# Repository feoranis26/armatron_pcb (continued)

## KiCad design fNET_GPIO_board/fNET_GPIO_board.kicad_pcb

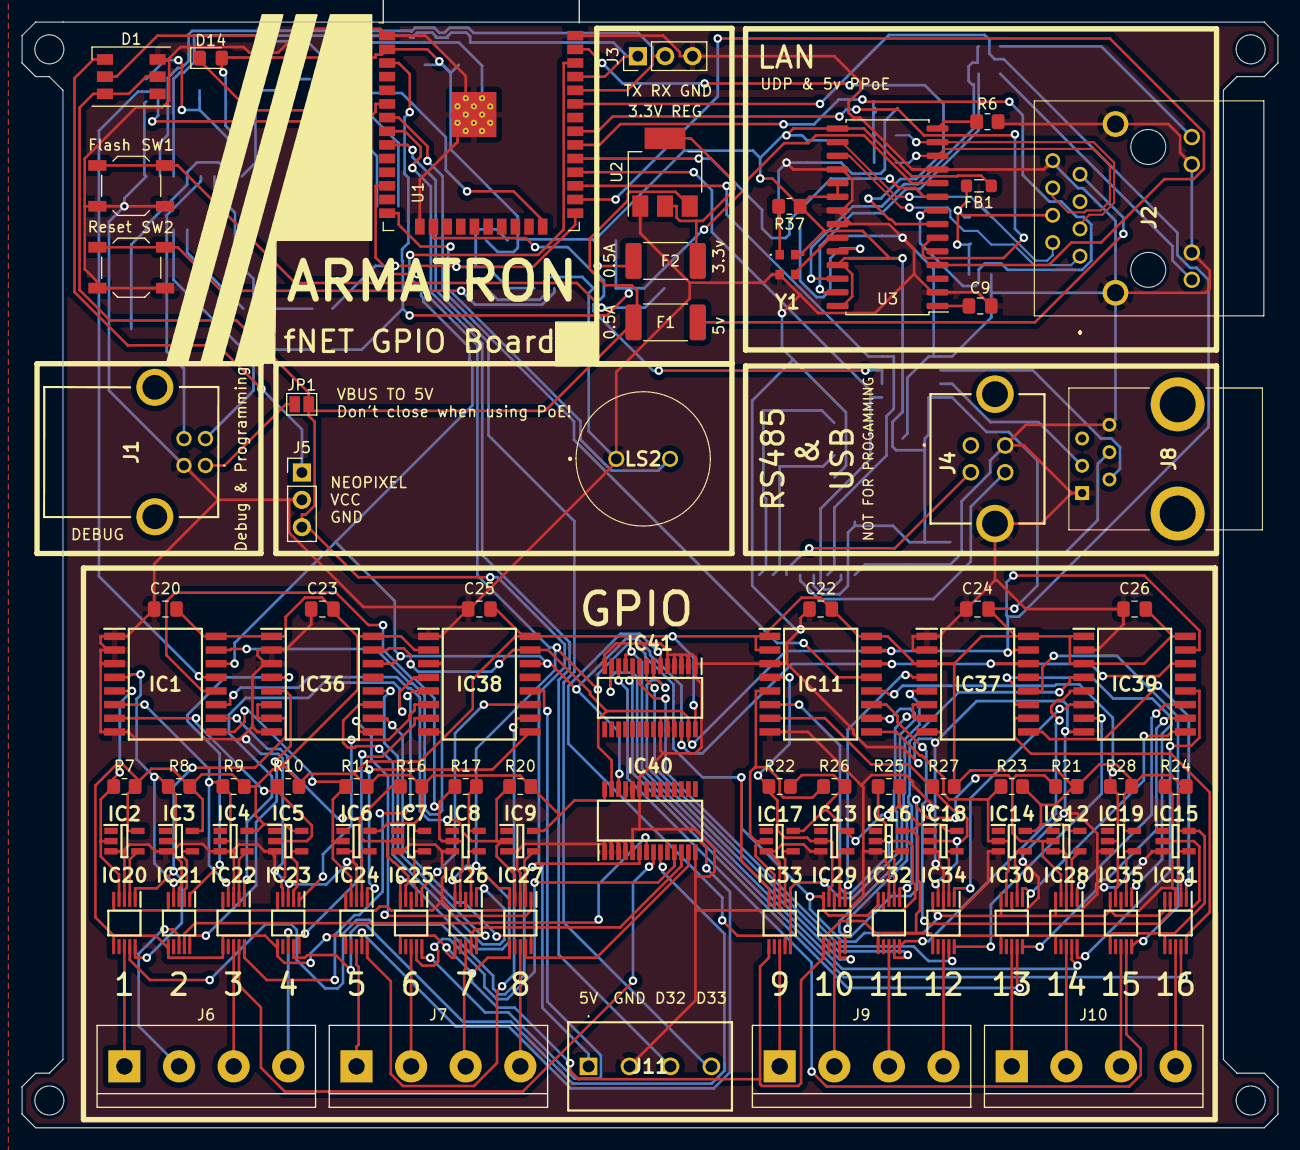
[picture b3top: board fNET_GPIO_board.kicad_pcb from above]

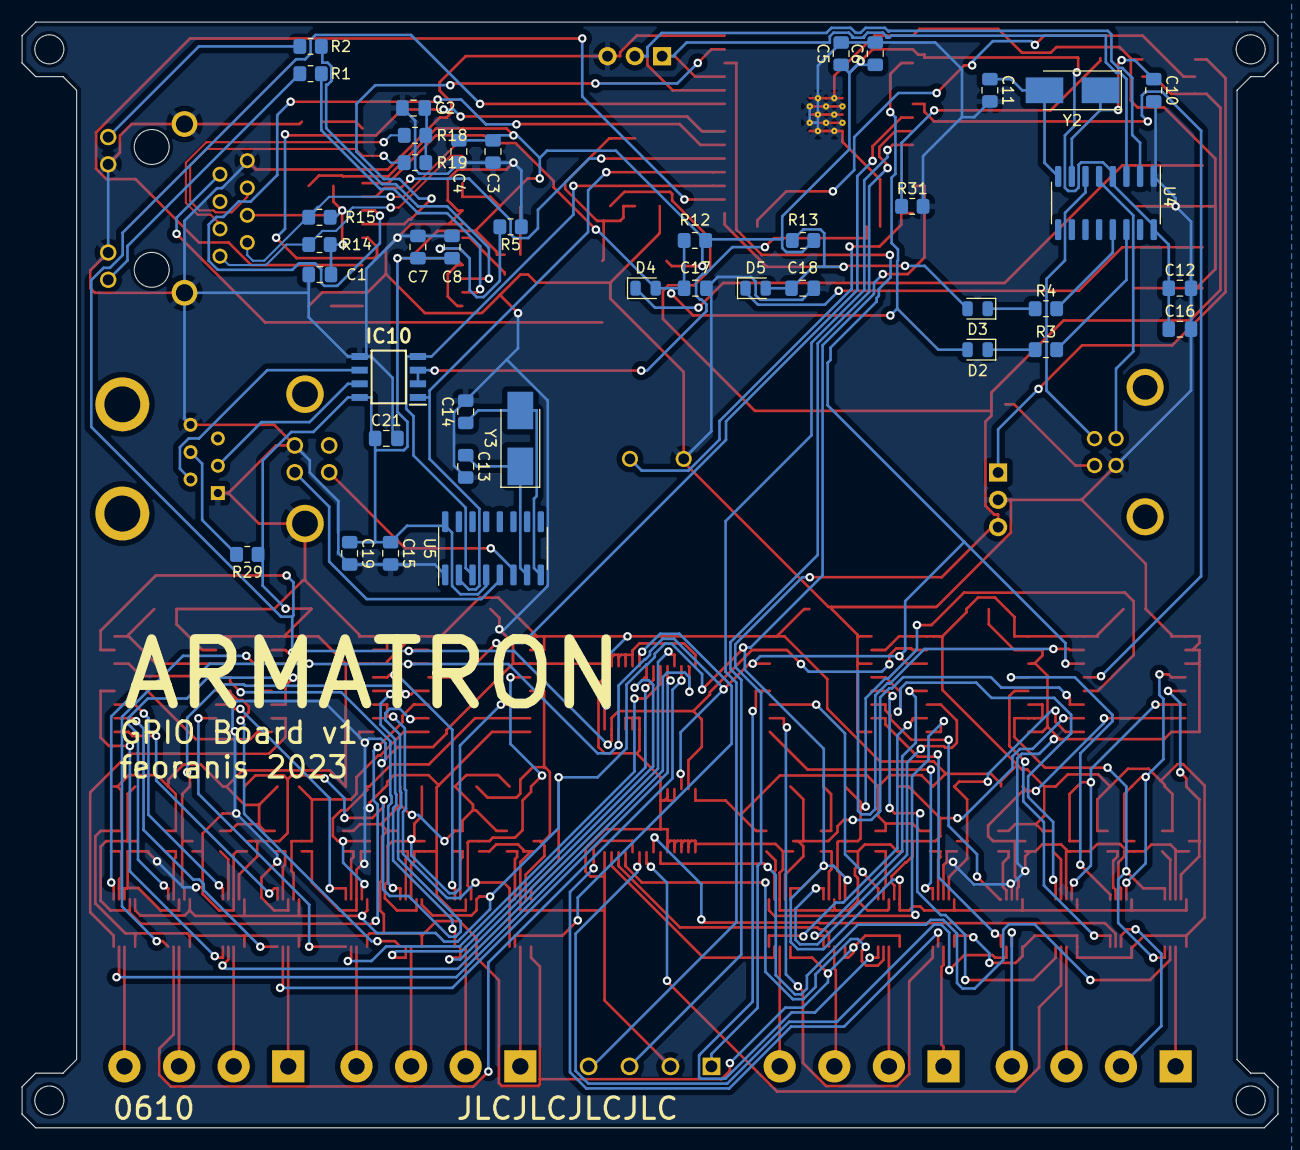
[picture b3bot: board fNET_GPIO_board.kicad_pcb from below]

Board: 2 copper layers, 116.8 x 102.9 mm, 134 parts (41 on the bottom side), 155 nets.

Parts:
C1, C2: 0.1uF; C_0805_2012Metric_Pad1.18x1.45mm_HandSolder
C3, C6, C7, C16, C17, C18, C19: 100n; C_0805_2012Metric_Pad1.18x1.45mm_HandSolder
C4, C8, C9: 10uF; C_0805_2012Metric_Pad1.18x1.45mm_HandSolder
C5: 10u; C_0805_2012Metric_Pad1.18x1.45mm_HandSolder
C10, C11, C13, C14: 22pF; C_0805_2012Metric_Pad1.18x1.45mm_HandSolder
C12, C15: 4.7u; C_0805_2012Metric_Pad1.18x1.45mm_HandSolder
C20, C21, C22, C23, C24, C25, C26: 1uf; C_0805_2012Metric_Pad1.18x1.45mm_HandSolder
D1: Inolux_IN-PI556FCH; LED_WS2812_PLCC6_5.0x5.0mm_P1.6mm
D2, D3, D4, D5: D; D_0805_2012Metric
D14: LED_Small; LED_0805_2012Metric_Pad1.15x1.40mm_HandSolder
F1, F2: 0.5A; Fuse_2512_6332Metric_Pad1.52x3.35mm_HandSolder
FB1: FerriteBead_Small; L_0805_2012Metric_Pad1.05x1.20mm_HandSolder
H1, H2, H3, H4: MountingHole; MountingHole_2.7mm_M2.5
IC1, IC11, IC36, IC37, IC38, IC39: PCF8574T_3,518; SOIC127P1032X265-16N
IC2, IC3, IC4, IC5, IC6, IC7, IC8, IC9, IC12, IC13, IC14, IC15, IC16, IC17, IC18, IC19: M74VHC1GT50DTT1G; SOT95P275X110-5N
IC10: MAX485ESA+; SOIC127P600X175-8N
IC20, IC21, IC22, IC23, IC24, IC25, IC26, IC27, IC28, IC29, IC30, IC31, IC32, IC33, IC34, IC35: MAX4634EUB+; SOP50P490X110-10N
IC40, IC41: PCA9685PW,118; SOP65P640X110-28N
J1: USB_B; USB1030GFPBB
J2: 5-2337992-4; 523379924
J3, J5: Conn_01x03_Pin; PinHeader_1x03_P2.54mm_Vertical
J4: USB_B; M701-330442
J6, J7, J9, J10: Screw_Terminal_01x04; TerminalBlock_bornier-4_P5.08mm
J8: 87180-064LF; 87180064LF
J11: Screw_Terminal_01x04; 2843924
JP1: SolderJumper_2_Open; SolderJumper-2_P1.3mm_Open_Pad1.0x1.5mm
LS2: PT-1241PFQ; PT1241PFQ
R1, R2: 220R; R_0805_2012Metric_Pad1.20x1.40mm_HandSolder
R3, R4, R5, R12, R13, R29, R37: 10K; R_0805_2012Metric_Pad1.20x1.40mm_HandSolder
R6: 2.32K 1%; R_0805_2012Metric_Pad1.20x1.40mm_HandSolder
R7, R8, R9, R10, R11, R16, R17, R20, R21, R22, R23, R24, R25, R26, R27, R28, R31: 1K; R_0805_2012Metric_Pad1.20x1.40mm_HandSolder
R14, R15, R18, R19: 50R; R_0805_2012Metric_Pad1.20x1.40mm_HandSolder
SW1, SW2: SW_Push; SW_SPST_TL3342
U1: ESP32-WROOM-32
U2: AMS1117-3.3; SOT-223-3_TabPin2
U3: ENC28J60x-SO; SOIC-28W_7.5x17.9mm_P1.27mm
U4, U5: CH340G; SOIC-16_3.9x9.9mm_P1.27mm
Y1: ECS-2520MVLC-250-BN-TR3; ECS2520MVLC250BNTR3
Y2, Y3: 12MHz; Crystal_SMD_5032-2Pin_5.0x3.2mm_HandSoldering

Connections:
+3.3V: C3.1, C4.1, C5.1, C6.1, C7.1, C8.1, C12.1, C15.1, C16.1, C19.1, C20.1, C21.1, C22.1, C23.1, C24.1, C25.1, C26.1, D14.2 (A), F2.2, FB1.1, IC1.16 (VDD), IC2.5 (VCC), IC3.5 (VCC), IC4.5 (VCC), IC5.5 (VCC), IC6.5 (VCC), IC7.5 (VCC), IC8.5 (VCC), IC9.5 (VCC), IC10.8 (VCC), IC11.1 (A0), IC11.2 (A1), IC11.16 (VDD), IC12.5 (VCC), IC13.5 (VCC), IC14.5 (VCC), IC15.5 (VCC), IC16.5 (VCC), IC17.5 (VCC), IC18.5 (VCC), IC19.5 (VCC), IC20.6 (V+), IC21.6 (V+), IC22.6 (V+), IC23.6 (V+), IC24.6 (V+), IC25.6 (V+), IC26.6 (V+), IC27.6 (V+), IC28.6 (V+), IC29.6 (V+), IC30.6 (V+), IC31.6 (V+), IC32.6 (V+), IC33.6 (V+), IC34.6 (V+), IC35.6 (V+), IC36.1 (A0), IC36.16 (VDD), IC37.3 (A2), IC37.16 (VDD), IC38.2 (A1), IC38.16 (VDD), IC39.1 (A0), IC39.3 (A2), IC39.16 (VDD), IC40.28 (VDD), IC41.28 (VDD), R7.1, R8.1, R9.1, R10.1, R11.1, R12.1, R13.1, R16.1, R17.1, R20.1, R21.1, R22.1, R23.1, R24.1, R25.1, R26.1, R27.1, R28.1, R29.1, R37.1, U1.2 (VDD), U3.15 (VDDTX), U3.19 (VDDRX), U3.20 (VDDPLL), U3.25 (VDDOSC), U3.28 (VDD), U4.4 (V3), U4.16 (VCC), U5.4 (V3), U5.16 (VCC), Y1.4 (VDD)
+5V: D1.3 (VDD), D1.5 (VCC), F1.1, J5.3, J11.1, JP1.2 (B), U2.3 (VI)
/Ethernet/LEDA: R1.2, U3.27 (LEDA)
/Ethernet/LEDB: R2.2, U3.26 (LEDB)
/Ethernet/RX+: J2.P3, R18.1, U3.13 (TPIN+)
/Ethernet/RX-: J2.P6, R19.2, U3.12 (TPIN-)
/Ethernet/TPOUT+: J2.P1, R14.2, U3.17 (TPOUT+)
/Ethernet/TPOUT-: J2.P2, R15.1, U3.16 (TPOUT-)
/Ethernet/TX_CT: C1.1, FB1.2, J2.P4, R14.1, R15.2
/GPIO Extender 1/GPIO Mux 0/A0: IC21.1 (A0), IC36.4 (P0)
/GPIO Extender 1/GPIO Mux 0/A1: IC21.10 (A1), IC36.5 (P1)
/GPIO Extender 1/GPIO Mux 0/IN: IC1.4 (P0), IC3.2 (INA), IC21.4 (NO3), R8.2
/GPIO Extender 1/GPIO Mux 1/A0: IC20.1 (A0), IC20.10 (A1), IC36.6 (P2), IC36.7 (P3)
/GPIO Extender 1/GPIO Mux 1/IN: IC1.5 (P1), IC2.2 (INA), IC20.4 (NO3), R7.2
/GPIO Extender 1/GPIO Mux 2/A0: IC22.1 (A0), IC38.4 (P0)
/GPIO Extender 1/GPIO Mux 2/A1: IC22.10 (A1), IC38.5 (P1)
/GPIO Extender 1/GPIO Mux 2/IN: IC1.6 (P2), IC4.2 (INA), IC22.4 (NO3), R9.2
/GPIO Extender 1/GPIO Mux 3/A0: IC23.1 (A0), IC38.6 (P2)
/GPIO Extender 1/GPIO Mux 3/A1: IC23.10 (A1), IC38.7 (P3)
/GPIO Extender 1/GPIO Mux 3/IN: IC1.7 (P3), IC5.2 (INA), IC23.4 (NO3), R10.2
/GPIO Extender 1/GPIO Mux 4/A0: IC24.1 (A0), IC38.9 (P4)
/GPIO Extender 1/GPIO Mux 4/A1: IC24.10 (A1), IC38.10 (P5)
/GPIO Extender 1/GPIO Mux 4/IN: IC1.9 (P4), IC6.2 (INA), IC24.4 (NO3), R11.2
/GPIO Extender 1/GPIO Mux 5/A0: IC25.1 (A0), IC38.11 (P6)
/GPIO Extender 1/GPIO Mux 5/A1: IC25.10 (A1), IC38.12 (P7)
/GPIO Extender 1/GPIO Mux 5/IN: IC1.10 (P5), IC7.2 (INA), IC25.4 (NO3), R16.2
/GPIO Extender 1/GPIO Mux 6/A0: IC27.1 (A0), IC36.9 (P4)
/GPIO Extender 1/GPIO Mux 6/A1: IC27.10 (A1), IC36.10 (P5)
/GPIO Extender 1/GPIO Mux 6/IN: IC1.11 (P6), IC9.2 (INA), IC27.4 (NO3), R20.2
/GPIO Extender 1/GPIO Mux 7/A0: IC26.1 (A0), IC36.11 (P6)
/GPIO Extender 1/GPIO Mux 7/A1: IC26.10 (A1), IC36.12 (P7)
/GPIO Extender 1/GPIO Mux 7/IN: IC1.12 (P7), IC8.2 (INA), IC26.4 (NO3), R17.2
/GPIO Extender 1/OUT_1: IC20.8 (COM), J6.1
/GPIO Extender 1/OUT_2: IC21.8 (COM), J6.2
/GPIO Extender 1/OUT_3: IC22.8 (COM), J6.3
/GPIO Extender 1/OUT_4: IC23.8 (COM), J6.4
/GPIO Extender 1/OUT_5: IC24.8 (COM), J7.1
/GPIO Extender 1/OUT_6: IC25.8 (COM), J7.2
/GPIO Extender 1/OUT_7: IC26.8 (COM), J7.3
/GPIO Extender 1/OUT_8: IC27.8 (COM), J7.4
/GPIO Extender 1/PWM_0: IC20.9 (NO2), IC40.6 (LED0)
/GPIO Extender 1/PWM_1: IC21.9 (NO2), IC40.7 (LED1)
/GPIO Extender 1/PWM_2: IC22.9 (NO2), IC40.8 (LED2)
/GPIO Extender 1/PWM_3: IC23.9 (NO2), IC40.9 (LED3)
/GPIO Extender 1/PWM_4: IC24.9 (NO2), IC40.10 (LED4)
/GPIO Extender 1/PWM_5: IC25.9 (NO2), IC40.11 (LED5)
/GPIO Extender 1/PWM_6: IC26.9 (NO2), IC40.12 (LED6)
/GPIO Extender 1/PWM_7: IC27.9 (NO2), IC40.13 (LED7)
/GPIO Extender 2/GPIO Mux 0/A0: IC29.1 (A0), IC37.4 (P0)
/GPIO Extender 2/GPIO Mux 0/A1: IC29.10 (A1), IC37.5 (P1)
/GPIO Extender 2/GPIO Mux 0/IN: IC11.4 (P0), IC13.2 (INA), IC29.4 (NO3), R22.2
/GPIO Extender 2/GPIO Mux 1/A0: IC33.1 (A0), IC33.10 (A1), IC37.6 (P2), IC37.7 (P3)
/GPIO Extender 2/GPIO Mux 1/IN: IC11.5 (P1), IC17.2 (INA), IC33.4 (NO3), R26.2
/GPIO Extender 2/GPIO Mux 2/A0: IC32.1 (A0), IC39.4 (P0)
/GPIO Extender 2/GPIO Mux 2/A1: IC32.10 (A1), IC39.5 (P1)
/GPIO Extender 2/GPIO Mux 2/IN: IC11.6 (P2), IC16.2 (INA), IC32.4 (NO3), R25.2
/GPIO Extender 2/GPIO Mux 3/A0: IC34.1 (A0), IC39.6 (P2)
/GPIO Extender 2/GPIO Mux 3/A1: IC34.10 (A1), IC39.7 (P3)
/GPIO Extender 2/GPIO Mux 3/IN: IC11.7 (P3), IC18.2 (INA), IC34.4 (NO3), R27.2
/GPIO Extender 2/GPIO Mux 4/A0: IC30.1 (A0), IC39.9 (P4)
/GPIO Extender 2/GPIO Mux 4/A1: IC30.10 (A1), IC39.10 (P5)
/GPIO Extender 2/GPIO Mux 4/IN: IC11.9 (P4), IC14.2 (INA), IC30.4 (NO3), R23.2
/GPIO Extender 2/GPIO Mux 5/A0: IC28.1 (A0), IC39.11 (P6)
/GPIO Extender 2/GPIO Mux 5/A1: IC28.10 (A1), IC39.12 (P7)
/GPIO Extender 2/GPIO Mux 5/IN: IC11.10 (P5), IC12.2 (INA), IC28.4 (NO3), R21.2
/GPIO Extender 2/GPIO Mux 6/A0: IC31.1 (A0), IC37.9 (P4)
/GPIO Extender 2/GPIO Mux 6/A1: IC31.10 (A1), IC37.10 (P5)
/GPIO Extender 2/GPIO Mux 6/IN: IC11.11 (P6), IC15.2 (INA), IC31.4 (NO3), R24.2
/GPIO Extender 2/GPIO Mux 7/A0: IC35.1 (A0), IC37.11 (P6)
/GPIO Extender 2/GPIO Mux 7/A1: IC35.10 (A1), IC37.12 (P7)
/GPIO Extender 2/GPIO Mux 7/IN: IC11.12 (P7), IC19.2 (INA), IC35.4 (NO3), R28.2
/GPIO Extender 2/OUT_1: IC33.8 (COM), J9.1
/GPIO Extender 2/OUT_2: IC29.8 (COM), J9.2
/GPIO Extender 2/OUT_3: IC32.8 (COM), J9.3
/GPIO Extender 2/OUT_4: IC34.8 (COM), J9.4
/GPIO Extender 2/OUT_5: IC30.8 (COM), J10.1
/GPIO Extender 2/OUT_6: IC28.8 (COM), J10.2
/GPIO Extender 2/OUT_7: IC35.8 (COM), J10.3
/GPIO Extender 2/OUT_8: IC31.8 (COM), J10.4
/GPIO Extender 2/PWM_0: IC33.9 (NO2), IC41.6 (LED0)
/GPIO Extender 2/PWM_1: IC29.9 (NO2), IC41.7 (LED1)
/GPIO Extender 2/PWM_2: IC32.9 (NO2), IC41.8 (LED2)
/GPIO Extender 2/PWM_3: IC34.9 (NO2), IC41.9 (LED3)
/GPIO Extender 2/PWM_4: IC30.9 (NO2), IC41.10 (LED4)
/GPIO Extender 2/PWM_5: IC28.9 (NO2), IC41.11 (LED5)
/GPIO Extender 2/PWM_6: IC35.9 (NO2), IC41.12 (LED6)
/GPIO Extender 2/PWM_7: IC31.9 (NO2), IC41.13 (LED7)
/Serial/A: IC10.6 (A), J8.2
/Serial/B: IC10.7 (B), J8.3
/Serial/INTR: J8.4, R29.2
/USB/VBUS: J1.1 (VBUS), JP1.1 (A)
/USB/nDTR: R4.2, U4.13 (~DTR)
/USB/nRTS: R3.2, U4.14 (~RTS)
DE: IC10.2 (~RE), IC10.3 (DE), U1.16 (IO13)
ETH_CS: U1.29 (IO5), U3.9 (~CS)
ETH_INTER: U1.26 (IO4), U3.4 (~INT)
EX1_INT: IC1.13 (~INT), U1.6 (IO34)
EX2_INT: IC11.13 (~INT), U1.7 (IO35)
FLASH_UART: D3.1 (K), R4.1
GND: C1.2, C2.2, C3.2, C4.2, C5.2, C6.2, C7.2, C8.2, C9.2, C10.2, C11.2, C12.2, C13.2, C14.2, C15.2, C16.2, C17.2, C18.2, C19.2, C20.2, C21.2, C22.2, C23.2, C24.2, C25.2, C26.2, D1.6 (VSS), IC1.1 (A0), IC1.2 (A1), IC1.3 (A2), IC1.8 (VSS), IC2.3 (GND), IC3.3 (GND), IC4.3 (GND), IC5.3 (GND), IC6.3 (GND), IC7.3 (GND), IC8.3 (GND), IC9.3 (GND), IC10.5 (GND), IC11.3 (A2), IC11.8 (VSS), IC12.3 (GND), IC13.3 (GND), IC14.3 (GND), IC15.3 (GND), IC16.3 (GND), IC17.3 (GND), IC18.3 (GND), IC19.3 (GND), IC20.3 (GND), IC21.3 (GND), IC22.3 (GND), IC23.3 (GND), IC24.3 (GND), IC25.3 (GND), IC26.3 (GND), IC27.3 (GND), IC28.3 (GND), IC29.3 (GND), IC30.3 (GND), IC31.3 (GND), IC32.3 (GND), IC33.3 (GND), IC34.3 (GND), IC35.3 (GND), IC36.2 (A1), IC36.3 (A2), IC36.8 (VSS), IC37.1 (A0), IC37.2 (A1), IC37.8 (VSS), IC38.1 (A0), IC38.3 (A2), IC38.8 (VSS), IC39.2 (A1), IC39.8 (VSS), IC40.1 (A0), IC40.2 (A1), IC40.3 (A2), IC40.4 (A3), IC40.5 (A4), IC40.14 (VSS), IC40.23 (~OE), IC40.24 (A5), IC40.25 (EXTCLK), IC41.1 (A0), IC41.2 (A1), IC41.3 (A2), IC41.4 (A3), IC41.5 (A4), IC41.14 (VSS), IC41.23 (~OE), IC41.24 (A5), IC41.25 (EXTCLK), J1.4 (GND), J2.MH1, J2.MH2, J2.P8, J2.P10, J2.P11, J3.3, J4.4 (GND), J4.5 (Shield), J5.2, J8.1, J8.6, J11.2, LS2.1 (-), R5.1, R6.2, R31.2, SW1.2, SW2.2, U1.1 (GND), U1.15 (GND), U1.38 (GND), U1.39 (GND), U2.1 (GND), U3.2 (VSS), U3.11 (VSSRX), U3.18 (VSSTX), U3.21 (VSSPLL), U3.22 (VSSOSC), U4.1 (GND), U5.1 (GND), Y1.2 (GND)
GPIO_1: J11.3, U1.8 (IO32)
GPIO_2: J11.4, U1.9 (IO33)
GPIO_ENA: IC20.5 (EN), IC21.5 (EN), IC22.5 (EN), IC23.5 (EN), IC24.5 (EN), IC25.5 (EN), IC26.5 (EN), IC27.5 (EN), IC28.5 (EN), IC29.5 (EN), IC30.5 (EN), IC31.5 (EN), IC32.5 (EN), IC33.5 (EN), IC34.5 (EN), IC35.5 (EN), U1.12 (IO27)
MISO: U1.31 (IO19), U3.6 (SO)
MOSI: U1.37 (IO23), U3.7 (SI)
NEOPIXEL: D1.2 (DIN), U1.24 (IO2)
unnamed: C2.1, R18.2, R19.1
unnamed: D1.1 (DO), J5.1
unnamed: D4.1 (K), SW1.1
unnamed: D5.1 (K), SW2.1
unnamed: D14.1 (K), R31.1
unnamed: F1.2, J2.P7
unnamed: IC2.4 (OUT_Y), IC20.2 (NO1)
unnamed: IC12.4 (OUT_Y), IC28.2 (NO1)
unnamed: IC13.4 (OUT_Y), IC29.2 (NO1)
unnamed: IC14.4 (OUT_Y), IC30.2 (NO1)
unnamed: IC15.4 (OUT_Y), IC31.2 (NO1)
unnamed: IC16.4 (OUT_Y), IC32.2 (NO1)
unnamed: IC17.4 (OUT_Y), IC33.2 (NO1)
unnamed: IC18.4 (OUT_Y), IC34.2 (NO1)
unnamed: IC19.4 (OUT_Y), IC35.2 (NO1)
unnamed: IC3.4 (OUT_Y), IC21.2 (NO1)
unnamed: IC4.4 (OUT_Y), IC22.2 (NO1)
unnamed: IC5.4 (OUT_Y), IC23.2 (NO1)
unnamed: IC6.4 (OUT_Y), IC24.2 (NO1)
unnamed: IC7.4 (OUT_Y), IC25.2 (NO1)
unnamed: IC8.4 (OUT_Y), IC26.2 (NO1)
unnamed: IC9.4 (OUT_Y), IC27.2 (NO1)
unnamed: J1.3 (D+), U4.5 (UD+)
unnamed: J1.2 (D-), U4.6 (UD-)
unnamed: J2.P9, R1.1
unnamed: J2.P12, R2.1
unnamed: J4.3 (D+), U5.5 (UD+)
unnamed: J4.2 (D-), U5.6 (UD-)
unnamed: F2.1, U2.2 (VO)
unnamed: U3.23 (OSC1), Y1.3 (OUTPUT)
unnamed: R5.2, U3.24 (OSC2)
unnamed: R6.1, U3.14 (RBIAS)
unnamed: C9.1, U3.1 (VCAP)
unnamed: C10.1, U4.7 (XI), Y2.1
unnamed: C11.1, U4.8 (XO), Y2.2
unnamed: C13.1, U5.7 (XI), Y3.1
unnamed: C14.1, U5.8 (XO), Y3.2
unnamed: R37.2, Y1.1 (TRI-STATE)
PIEZO: LS2.2 (+), U1.14 (IO12)
PIN_FLASH: C18.1, D3.2 (A), D5.2 (A), R13.2, U1.25 (IO0)
PIN_RESET: C17.1, D2.2 (A), D4.2 (A), R12.2, U1.3 (EN), U3.10 (~RESET)
RESET_UART: D2.1 (K), R3.1
RX: J3.2, U1.34 (RXD0/IO3), U4.2 (TXD)
RX2: IC10.1 (RO), U1.28 (IO17), U5.2 (TXD)
SCK: U1.30 (IO18), U3.8 (SCK)
SCL: IC1.14 (SCL), IC11.14 (SCL), IC36.14 (SCL), IC37.14 (SCL), IC38.14 (SCL), IC39.14 (SCL), IC40.26 (SCL), IC41.26 (SCL), U1.36 (IO22)
SDA: IC1.15 (SDA), IC11.15 (SDA), IC36.15 (SDA), IC37.15 (SDA), IC38.15 (SDA), IC39.15 (SDA), IC40.27 (SDA), IC41.27 (SDA), U1.33 (IO21)
TX: J3.1, U1.35 (TXD0/IO1), U4.3 (RXD)
TX2: IC10.4 (DI), U1.27 (IO16), U5.3 (RXD)

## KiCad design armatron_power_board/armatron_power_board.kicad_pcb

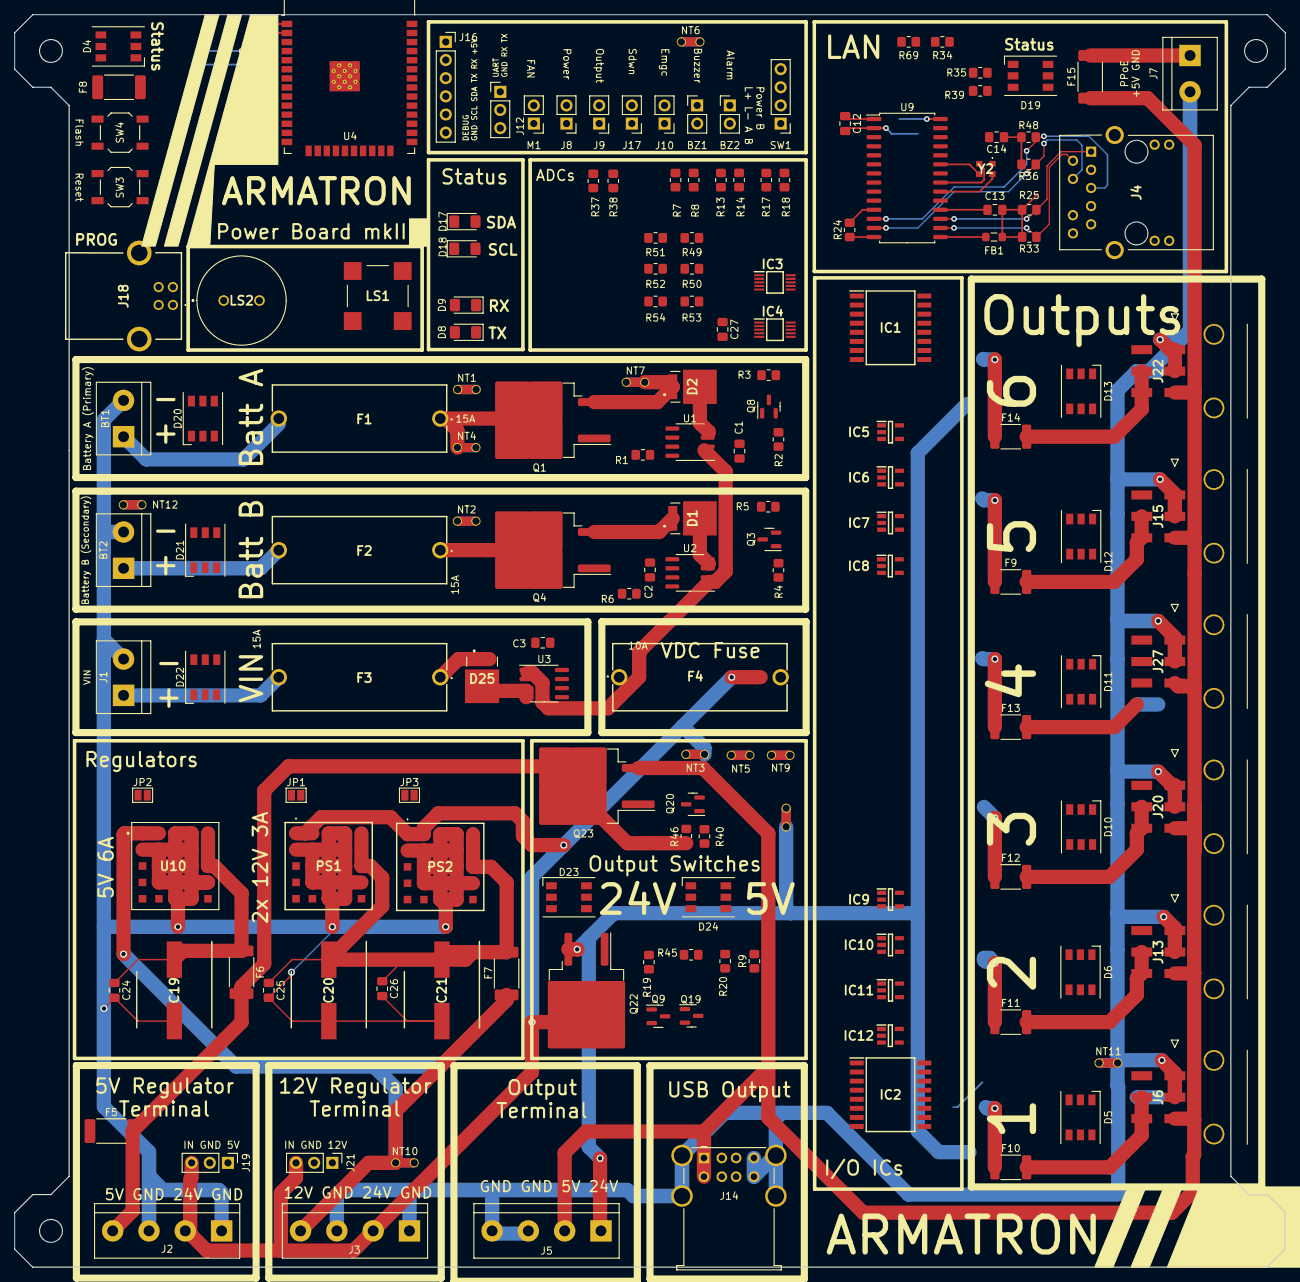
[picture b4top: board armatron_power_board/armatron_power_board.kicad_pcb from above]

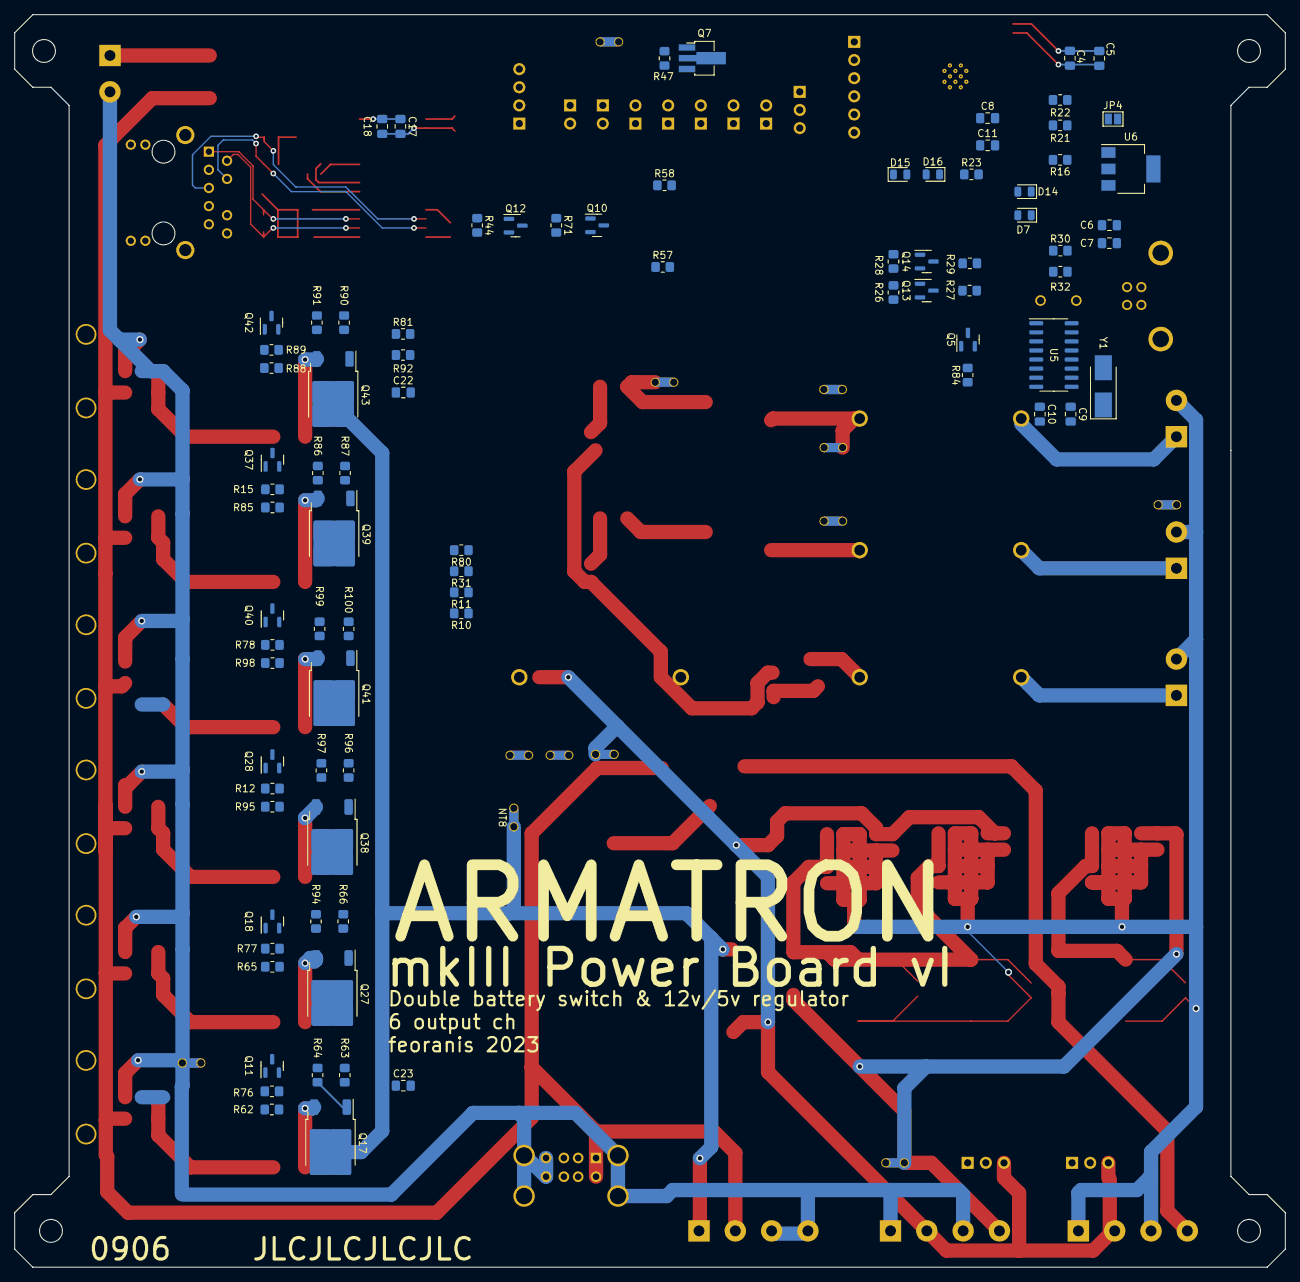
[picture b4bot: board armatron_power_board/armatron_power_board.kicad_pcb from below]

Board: 2 copper layers, 177.8 x 175.3 mm, 249 parts (85 on the bottom side), 188 nets.

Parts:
BT1: Battery A (Primary); TerminalBlock_bornier-2_P5.08mm
BT2: Battery B (Secondary); TerminalBlock_bornier-2_P5.08mm
BZ1, BZ2: Buzzer; PinHeader_1x02_P2.54mm_Vertical
C1, C2, C3: 1n; C_0805_2012Metric_Pad1.18x1.45mm_HandSolder
C4, C7, C8, C11, C18: 100n; C_0805_2012Metric_Pad1.18x1.45mm_HandSolder
C5, C22, C23, C27: 10u; C_0805_2012Metric_Pad1.18x1.45mm_HandSolder
C6: 4.7u; C_0805_2012Metric_Pad1.18x1.45mm_HandSolder
C9, C10: 22pF; C_0805_2012Metric_Pad1.18x1.45mm_HandSolder
C12, C17: 10uF; C_0805_2012Metric_Pad1.18x1.45mm_HandSolder
C13, C14: 0.1uF; C_0805_2012Metric_Pad1.18x1.45mm_HandSolder
C19, C20, C21: MAL215097001E3; CAPAE1050X1050N
C24, C25, C26: 1uF; C_0805_2012Metric_Pad1.18x1.45mm_HandSolder
D1, D2, D25: V15PM15HM3_H; V10P20M386A
D4, D5, D6, D10, D11, D12, D13, D19, D20, D21, D22, D23, D24: Inolux_IN-PI556FCH; LED_WS2812_PLCC6_5.0x5.0mm_P1.6mm
D7, D14, D15, D16: D; D_0805_2012Metric
D8, D9, D17, D18: LED; LED_1206_3216Metric_Pad1.42x1.75mm_HandSolder
F1, F2, F3, F4: 10A; WR-FSH_THT_2
F5, F8: 0.5A; Fuse_2512_6332Metric_Pad1.52x3.35mm_HandSolder
F6, F15: 5A; Fuse_2512_6332Metric_Pad1.52x3.35mm_HandSolder
F7: 3.5A; Fuse_2512_6332Metric_Pad1.52x3.35mm_HandSolder
F9, F10, F11, F12, F13, F14: 10A; Fuse_1812_4532Metric_Pad1.30x3.40mm_HandSolder
FB1: FerriteBead_Small; L_0805_2012Metric_Pad1.05x1.20mm_HandSolder
IC1, IC2: PCF8574T_3,518; SOIC127P1032X265-16N
IC3, IC4: ADS1115BQDGSRQ1; SOP50P490X110-10N
IC5, IC6, IC7, IC8, IC9, IC10, IC11, IC12: M74VHC1GT50DTT1G; SOT95P275X110-5N
J1: Conn_01x02; TerminalBlock_bornier-2_P5.08mm
J2, J3, J5: Screw_Terminal_01x04; TerminalBlock_bornier-4_P5.08mm
J4: 74982104400
J6, J13, J15, J20, J22, J27: 3-794620-6; 43045-06YY_060708_1
J7: Screw_Terminal_01x02; TerminalBlock_bornier-2_P5.08mm
J8, J9, J10, J17: Conn_01x02; PinHeader_1x02_P2.54mm_Vertical
J12, J19, J21: Conn_01x03_Pin; PinHeader_1x03_P2.54mm_Vertical
J14: USB_A_Stacked; USB_A_Wuerth_61400826021_Horizontal_Stacked
J16: Conn_01x06_Socket; PinSocket_1x06_P2.54mm_Vertical
J18: USB_B; USB1030GFPBB
JP1, JP2, JP3, JP4: SolderJumper_2_Open; SolderJumper-2_P1.3mm_Open_Pad1.0x1.5mm
LS1: CMT-8504-100-SMT-TR; CMT8504100SMTTR
LS2: PT-1241PFQ; PT1241PFQ
M1: Fan; PinHeader_1x02_P2.54mm_Vertical
MH1, MH2, MH3, MH4: MountingHole_3.2mm_M3
NT1, NT2, NT3, NT4, NT5, NT6, NT7, NT8, NT9, NT10, NT11, NT12: NetTie_2; NetTie-2_THT_Pad1.0mm
PS1, PS2: RPMB12-2.0-CT; RPMB1220CT
Q1, Q4, Q22, Q23: IRF4905; TO-263-2
Q3, Q5, Q8, Q9, Q10, Q11, Q12, Q13, Q14, Q18, Q19, Q20, Q28, Q37, Q40, Q42: BC817; SOT-23
Q7: Q_NPN_BCE; SOT-89-3_Handsoldering
Q17, Q27, Q38, Q39, Q41, Q43: Q_PNP_Darlington_BCE; TO-252-2
R1, R2, R3, R4, R5, R6, R9, R16, R19, R30, R32, R40, R45, R46, R62, R63, R64, R65, R66, R71, R84, R85, R86, R87, R88, R90, R91, R94, R95, R96, R97, R98, R99, R100: 1K; R_0805_2012Metric_Pad1.20x1.40mm_HandSolder
R7, R13, R17, R37: 220K; R_0805_2012Metric_Pad1.20x1.40mm_HandSolder
R8, R14, R18, R38: 27K; R_0805_2012Metric_Pad1.20x1.40mm_HandSolder
R10, R11, R12, R15, R31, R76, R77, R78, R80, R81, R89, R92: 100K; R_0805_2012Metric_Pad1.20x1.40mm_HandSolder
R20, R21, R22, R23, R26, R28, R34, R44, R47, R69: 10K; R_0805_2012Metric_Pad1.20x1.40mm_HandSolder
R24: 2.32K 1%; R_0805_2012Metric_Pad1.20x1.40mm_HandSolder
R25, R33, R36, R48: 50R; R_0805_2012Metric_Pad1.20x1.40mm_HandSolder
R27, R29, R57, R58: 1k; R_0805_2012Metric_Pad1.20x1.40mm_HandSolder
R35, R39: 220R; R_0805_2012Metric_Pad1.20x1.40mm_HandSolder
R49, R51, R53: 22K; R_0805_2012Metric_Pad1.20x1.40mm_HandSolder
R50, R52, R54: 15K; R_0805_2012Metric_Pad1.20x1.40mm_HandSolder
SW1: SW_Push_LED; PinHeader_1x04_P2.54mm_Vertical
SW3, SW4: SW_Push; SW_SPST_TL3342
U1, U2, U3: ACS712xLCTR-20A; SOIC-8_3.9x4.9mm_P1.27mm
U4: ESP32-WROOM-32
U5: CH340G; SOIC-16_3.9x9.9mm_P1.27mm
U6: AMS1117-3.3; SOT-223-3_TabPin2
U9: ENC28J60x-SO; SOIC-28W_7.5x17.9mm_P1.27mm
U10: RPM5.0-6.0; RPM5060
Y1: 12MHz; Crystal_SMD_5032-2Pin_5.0x3.2mm_HandSoldering
Y2: ECS-2520MVLC-250-BN-TR3; ECS2520MVLC250BNTR3

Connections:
5V_Enable: R40.2, U4.10 (IO25), U4.12 (IO27)
5V_POWER: F5.2, F6.2, J2.4, Q23.2 (D), R46.1
5V_adc: D4.3 (VDD), D4.5 (VCC), D5.3 (VDD), D5.5 (VCC), D6.3 (VDD), D6.5 (VCC), D10.3 (VDD), D10.5 (VCC), D11.3 (VDD), D11.5 (VCC), D12.3 (VDD), D12.5 (VCC), D13.3 (VDD), D13.5 (VCC), D19.3 (VDD), D19.5 (VCC), D20.3 (VDD), D20.5 (VCC), D21.3 (VDD), D21.5 (VCC), D22.3 (VDD), D22.5 (VCC), D23.3 (VDD), D23.5 (VCC), D24.3 (VDD), D24.5 (VCC), F5.1, IC3.6 (AIN2), J4.9 (V2+), J16.1, J19.1, JP4.2 (B), LS1.1 (+), U1.8 (VCC), U2.8 (VCC), U3.8 (VCC), U6.3 (VI)
5V_out: F15.1, J5.2, J6.3, J13.3, J14.1 (VBUS1), J14.5 (VBUS2), J15.3, J20.3, J22.3, J27.3, Q23.3 (S)
12V_POWER: F7.2, J3.4, NT10.1, U10.A1 (+VIN), U10.A2 (+VIN)
12V_adc: IC3.7 (AIN3), R37.2, R38.1
12V_ok: JP2.1 (A), PS1.D1 (PGOOD)
24V_Enable: R9.2, U4.11 (IO26)
24V_out: J5.1, NT8.1, Q17.2 (C), Q22.3 (S), Q27.2 (C), Q38.2 (C), Q39.2 (C), Q41.2 (C), Q43.2 (C), R63.1, R66.1, R86.1, R90.1, R96.1, R99.1
+3.3V: C4.1, C5.1, C6.1, C7.1, C17.1, C18.1, C22.1, C23.1, C27.1, D8.2 (A), D9.2 (A), D17.2 (A), D18.2 (A), F8.2, FB1.1, IC1.16 (VDD), IC2.1 (A0), IC2.16 (VDD), IC3.1 (ADDR), IC3.8 (VDD), IC4.1 (ADDR), IC4.8 (VDD), IC5.5 (VCC), IC6.5 (VCC), IC7.5 (VCC), IC8.5 (VCC), IC9.5 (VCC), IC10.5 (VCC), IC11.5 (VCC), IC12.5 (VCC), R10.1, R11.1, R16.1, R21.1, R22.1, R23.1, R31.1, R34.1, R80.1, R81.1, R92.1, U4.2 (VDD), U5.4 (V3), U5.16 (VCC), U9.15 (VDDTX), U9.19 (VDDRX), U9.20 (VDDPLL), U9.25 (VDDOSC), U9.28 (VDD), Y2.4 (VDD)
+12V: BZ1.2 (-), BZ2.2 (-), J21.1, M1.1 (+), NT10.2, R37.1
+VDC: F4.2, J2.2, J3.2, J19.3, J21.3, JP1.1 (A), JP3.1 (A), NT3.2, NT5.2, NT9.1, PS1.A1 (VIN_1), PS1.A2 (VIN_2), PS2.A1 (VIN_1), PS2.A2 (VIN_2), Q22.2 (D), R45.1
/LEDA: R35.2, U9.27 (LEDA)
/LEDB: R39.2, U9.26 (LEDB)
/RX+: J4.4 (RD+), R36.1, U9.13 (TPIN+)
/RX-: J4.5 (RD-), R48.2, U9.12 (TPIN-)
/TPOUT+: J4.1 (TD+), R25.2, U9.17 (TPOUT+)
/TPOUT-: J4.2 (TD-), R33.1, U9.16 (TPOUT-)
/TX_CT: C13.1, FB1.2, J4.3 (CD), R25.1, R33.2
BATT_A_IN: F1.1, NT1.2, NT4.1, Q1.2 (D), R1.1
BATT_A_LATCH: D2.3 (K), U1.3 (IP-), U1.4 (IP-)
BATT_A_SW: D2.1 (A_1), D2.2 (A_2), NT7.2, Q1.3 (S)
BATT_B_IN: F2.1, NT2.2, Q4.2 (D), R6.1
BATT_B_LATCH: D1.3 (K), U2.3 (IP-), U2.4 (IP-)
BATT_B_SW: D1.1 (A_1), D1.2 (A_2), Q4.3 (S)
D+: J18.3 (D+), U5.5 (UD+)
D-: J18.2 (D-), U5.6 (UD-)
ETH_CS: U4.29 (IO5), U9.9 (~CS)
ETH_INTER: U4.26 (IO4), U9.4 (~INT)
FLASH_UART: D16.1 (K), R32.1
GND: C1.2, C2.2, C3.2, C4.2, C5.2, C6.2, C7.2, C8.2, C9.2, C10.2, C11.2, C12.2, C13.2, C14.2, C17.2, C18.2, C22.2, C23.2, C27.2, D4.6 (VSS), D5.6 (VSS), D6.6 (VSS), D10.6 (VSS), D11.6 (VSS), D12.6 (VSS), D13.6 (VSS), D19.6 (VSS), D20.6 (VSS), D21.6 (VSS), D22.6 (VSS), D23.6 (VSS), D24.6 (VSS), IC1.1 (A0), IC1.2 (A1), IC1.3 (A2), IC1.8 (VSS), IC2.2 (A1), IC2.3 (A2), IC2.8 (VSS), IC3.3 (GND), IC4.3 (GND), IC5.3 (GND), IC6.3 (GND), IC7.3 (GND), IC8.3 (GND), IC9.3 (GND), IC10.3 (GND), IC11.3 (GND), IC12.3 (GND), J4.10 (V2-), J4.11 (A_GREEN/K_YELLOW_1), J4.13 (A_GREEN/K_YELLOW_2), J4.MH1, J4.MH2, J8.2, J9.2, J10.2, J12.3, J16.6, J17.2, J18.4 (GND), LS2.1 (-), NT6.1, NT11.1, NT12.1, Q3.2 (E), Q5.2 (E), Q7.3 (E), Q8.2 (E), Q9.2 (E), Q10.2 (E), Q11.2 (E), Q12.2 (E), Q13.2 (E), Q14.2 (E), Q18.2 (E), Q19.2 (E), Q20.2 (E), Q28.2 (E), Q37.2 (E), Q40.2 (E), Q42.2 (E), R3.2, R5.2, R8.2, R12.1, R14.2, R15.1, R18.2, R24.2, R38.2, R50.2, R52.2, R54.2, R69.1, R76.1, R77.1, R78.1, R89.1, SW1.3 (K), SW3.2, SW4.2, U1.5 (GND), U2.5 (GND), U3.5 (GND), U4.1 (GND), U4.15 (GND), U4.38 (GND), U4.39 (GND), U5.1 (GND), U6.1 (GND), U9.2 (VSS), U9.11 (VSSRX), U9.18 (VSSTX), U9.21 (VSSPLL), U9.22 (VSSOSC), Y2.2 (GND)
MISO: U4.31 (IO19), U9.6 (SO)
MOSI: U4.37 (IO23), U9.7 (SI)
NEOPIXEL: D4.2 (DIN), U4.13 (IO14)
unnamed: BT1.1 (+), F1.2
unnamed: BT2.1 (+), F2.2
unnamed: BZ1.1 (+), Q10.3 (C)
unnamed: BZ2.1 (+), Q12.3 (C)
unnamed: C14.1, R36.2, R48.1
unnamed: C19.1 (+), C24.1, F6.1, U10.A5 (+VOUT), U10.B5 (+VOUT), U10.C5 (Sense)
unnamed: C20.1 (+), C21.1 (+), C25.1, C26.1, F7.1, PS1.A5 (VOUT_1), PS1.B5 (VOUT_2), PS1.C5 (SENSE), PS2.A5 (VOUT_1), PS2.B5 (VOUT_2), PS2.C5 (SENSE)
unnamed: D5.1 (DO), D6.2 (DIN)
unnamed: D8.1 (K), R27.2
unnamed: D9.1 (K), R29.2
unnamed: D6.1 (DO), D10.2 (DIN)
unnamed: D10.1 (DO), D11.2 (DIN)
unnamed: D11.1 (DO), D12.2 (DIN)
unnamed: D12.1 (DO), D13.2 (DIN)
unnamed: D13.1 (DO), D19.2 (DIN)
unnamed: D14.1 (K), SW3.1
unnamed: D15.1 (K), SW4.1
unnamed: D17.1 (K), R57.2
unnamed: D18.1 (K), R58.2
unnamed: D4.1 (DO), D20.2 (DIN)
unnamed: D20.1 (DO), D21.2 (DIN)
unnamed: D21.1 (DO), D22.2 (DIN)
unnamed: D22.1 (DO), D23.2 (DIN)
unnamed: D23.1 (DO), D24.2 (DIN)
unnamed: D5.2 (DIN), D24.1 (DO)
unnamed: D25.1 (A_1), D25.2 (A_2), F3.1
unnamed: F4.1, U1.1 (IP+), U1.2 (IP+), U2.1 (IP+), U2.2 (IP+), U3.1 (IP+), U3.2 (IP+)
unnamed: IC1.4 (P0), IC5.2 (INA)
unnamed: IC1.5 (P1), IC6.2 (INA)
unnamed: IC1.6 (P2), IC7.2 (INA)
unnamed: IC1.7 (P3), IC8.2 (INA)
unnamed: F3.2, J1.1
unnamed: J4.12 (K_GREEN/A_YELLOW_1), R35.1
unnamed: J4.14 (K_GREEN/A_YELLOW_2), R39.1
unnamed: F15.2, J7.1
unnamed: J8.1, NT9.2
unnamed: J9.1, NT8.2
unnamed: JP1.2 (B), PS1.C1 (CTRL)
unnamed: JP2.2 (B), U10.C1 (CTRL)
unnamed: JP3.2 (B), PS2.C1 (CTRL)
unnamed: LS1.2 (-), Q5.3 (C)
unnamed: M1.2 (-), Q7.2 (C)
unnamed: NT1.1, R7.1
unnamed: NT2.1, R13.1
unnamed: NT3.1, R17.1
unnamed: NT4.2, SW1.1
unnamed: NT7.1, SW1.2
unnamed: Q1.1 (G), Q8.3 (C), R1.2
unnamed: Q3.1 (B), R4.1, R5.1
unnamed: Q3.3 (C), Q4.1 (G), R6.2
unnamed: Q5.1 (B), R84.2
unnamed: Q7.1 (B), R47.2
unnamed: Q8.1 (B), R2.1, R3.1
unnamed: Q9.1 (B), R20.2
unnamed: Q9.3 (C), R9.1, R19.1
unnamed: Q10.1 (B), R71.2
unnamed: Q11.1 (B), R62.2
unnamed: Q11.3 (C), R63.2, R64.1
unnamed: Q12.1 (B), R44.2
unnamed: Q13.1 (B), R26.2
unnamed: Q13.3 (C), R27.1
unnamed: Q14.1 (B), R28.2
unnamed: Q14.3 (C), R29.1
unnamed: Q17.1 (B), R64.2
unnamed: F10.1, Q17.3 (E)
unnamed: Q18.1 (B), R65.2
unnamed: Q18.3 (C), R66.2, R94.1
unnamed: Q19.1 (B), R19.2
unnamed: Q19.3 (C), Q22.1 (G), R45.2
unnamed: Q20.1 (B), R40.1
unnamed: Q20.3 (C), Q23.1 (G), R46.2
unnamed: Q27.1 (B), R94.2
unnamed: F11.1, Q27.3 (E)
unnamed: Q28.1 (B), R95.2
unnamed: Q28.3 (C), R96.2, R97.1
unnamed: Q37.1 (B), R85.2
unnamed: Q37.3 (C), R86.2, R87.1
unnamed: Q38.1 (B), R97.2
unnamed: F12.1, Q38.3 (E)
unnamed: Q39.1 (B), R87.2
unnamed: F9.1, Q39.3 (E)
unnamed: Q40.1 (B), R98.2
unnamed: Q40.3 (C), R99.2, R100.1
unnamed: Q41.1 (B), R100.2
unnamed: F13.1, Q41.3 (E)
unnamed: Q42.1 (B), R88.2
unnamed: Q42.3 (C), R90.2, R91.1
unnamed: Q43.1 (B), R91.2
unnamed: F14.1, Q43.3 (E)
unnamed: NT5.1, SW1.4 (A)
unnamed: C1.1, U1.6 (FILTER)
unnamed: C2.1, U2.6 (FILTER)
unnamed: C3.1, U3.6 (FILTER)
unnamed: C9.1, U5.7 (XI), Y1.1
unnamed: C10.1, U5.8 (XO), Y1.2
unnamed: F8.1, U6.2 (VO)
unnamed: U9.23 (OSC1), Y2.3 (OUTPUT)
unnamed: R69.2, U9.24 (OSC2)
unnamed: R24.1, U9.14 (RBIAS)
unnamed: C12.1, U9.1 (VCAP)
unnamed: R34.2, Y2.1 (TRI-STATE)
PD_1: IC2.9 (P4), J6.4, R10.2
PD_2: IC2.10 (P5), J13.4, R11.2
PD_3: IC2.11 (P6), J20.4, R31.2
PD_4: IC2.12 (P7), J27.4, R80.2
PD_5: IC1.10 (P5), J15.4, R81.2
PD_6: IC1.11 (P6), J22.4, R92.2
PIEZO: LS2.2 (+), U4.23 (IO15)
PIEZO_LOUD: R84.1, U4.27 (IO16)
PIN_ADC_BATT_A: IC4.4 (AIN0), R7.2, R8.1
PIN_ADC_BATT_B: IC4.5 (AIN1), R13.2, R14.1
PIN_ADC_VIN: IC4.6 (AIN2), R17.2, R18.1
PIN_ALARM: IC6.4 (OUT_Y), R44.1
PIN_BATT_A_SENSE: R49.1, U1.7 (VIOUT)
PIN_BATT_A_SENSE_ADC: IC4.7 (AIN3), R49.2, R50.1
PIN_BATT_B_SENSE: R51.1, U2.7 (VIOUT)
PIN_BATT_B_SENSE_ADC: IC3.4 (AIN0), R51.2, R52.1
PIN_BUZZER: IC7.4 (OUT_Y), R71.1
PIN_EmergencyButton: J10.1, R16.2, R20.1, U4.7 (IO35)
PIN_FLASH: C11.1, D15.2 (A), D16.2 (A), R23.2, U4.25 (IO0)
PIN_Fan: IC5.4 (OUT_Y), R47.1
PIN_RESET: C8.1, D7.2 (A), D14.2 (A), R22.2, U4.3 (EN), U9.10 (~RESET)
PIN_Sdwn_Btn: J17.1, R21.2, U4.6 (IO34)
PIN_VBATT_A_ENBL: R2.2, U4.8 (IO32)
PIN_VBATT_B_ENBL: R4.2, U4.9 (IO33)
PIN_VIN_SENSE: R53.1, U3.7 (VIOUT)
PIN_VIN_SENSE_ADC: IC3.5 (AIN1), R53.2, R54.1
POWER_GND: BT1.2 (-), BT2.2 (-), C19.2 (-), C20.2 (-), C21.2 (-), C24.2, C25.2, C26.2, J1.2, J2.1, J2.3, J3.1, J3.3, J5.3, J5.4, J6.1, J6.2, J7.2, J13.1, J13.2, J14.4 (GND1), J14.8 (GND2), J14.9 (Shield), J15.1, J15.2, J19.2, J20.1, J20.2, J21.2, J22.1, J22.2, J27.1, J27.2, NT6.2, NT11.2, NT12.2, PS1.A3 (GND_1), PS1.A4 (GND_2), PS1.B1 (GND_3), PS1.B2 (GND_4), PS1.B3 (GND_5), PS1.B4 (GND_6), PS1.C2 (GND_7), PS1.C3 (GND_8), PS1.C4 (GND_9), PS1.D2 (GND_10), PS1.D3 (GND_11), PS1.D4 (GND_12), PS1.D5 (GND_13), PS1.E3 (GND_14), PS1.E4 (GND_15), PS2.A3 (GND_1), PS2.A4 (GND_2), PS2.B1 (GND_3), PS2.B2 (GND_4), PS2.B3 (GND_5), PS2.B4 (GND_6), PS2.C2 (GND_7), PS2.C3 (GND_8), PS2.C4 (GND_9), PS2.D2 (GND_10), PS2.D3 (GND_11), PS2.D4 (GND_12), PS2.D5 (GND_13), PS2.E3 (GND_14), PS2.E4 (GND_15), U10.A3 (GND), U10.A4 (GND), U10.B1 (GND), U10.B2 (GND), U10.B3 (GND), U10.B4 (GND), U10.C2 (GND), U10.C3 (GND), U10.C4 (GND), U10.D2 (GND), U10.D3 (GND), U10.D4 (GND), U10.D5 (GND), U10.E3 (GND), U10.E4 (GND)
POW_1: F10.2, J6.5, J6.6
POW_1_EN: IC9.4 (OUT_Y), R62.1, R76.2
POW_1_EN_O: IC2.4 (P0), IC9.2 (INA)
POW_2: F11.2, J13.5, J13.6
POW_2_EN: IC10.4 (OUT_Y), R65.1, R77.2
POW_2_EN_O: IC2.5 (P1), IC10.2 (INA)
POW_3: F12.2, J20.5, J20.6
POW_3_EN: IC11.4 (OUT_Y), R12.2, R95.1
POW_3_EN_O: IC2.6 (P2), IC11.2 (INA)
POW_4: F13.2, J27.5, J27.6
POW_4_EN: IC12.4 (OUT_Y), R78.2, R98.1
POW_4_EN_O: IC2.7 (P3), IC12.2 (INA)
POW_5: F9.2, J15.5, J15.6
POW_5_EN: IC8.4 (OUT_Y), R15.2, R85.1
POW_6: F14.2, J22.5, J22.6
POW_6_EN: IC1.9 (P4), R88.1, R89.2
RESET_UART: D7.1 (K), R30.1
RX: J12.2, J16.2, R28.1, U4.34 (RXD0/IO3), U5.2 (TXD)
SCK: U4.30 (IO18), U9.8 (SCK)
SCL: IC1.14 (SCL), IC2.14 (SCL), IC3.10 (SCL), IC4.10 (SCL), J16.5, R57.1, U4.36 (IO22)
SDA: IC1.15 (SDA), IC2.15 (SDA), IC3.9 (SDA), IC4.9 (SDA), J16.4, R58.1, U4.33 (IO21)
TX: J12.1, J16.3, R26.1, U4.35 (TXD0/IO1), U5.3 (RXD)
VBUS: J18.1 (VBUS), JP4.1 (A)
VIN: D25.3 (K), U3.3 (IP-), U3.4 (IP-)
nDTR: R32.2, U5.13 (~DTR)
nRTS: R30.2, U5.14 (~RTS)
